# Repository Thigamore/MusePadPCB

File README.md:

# MusePadPCB  
  
  A small PCB which contains 4 keys so that I can try and make it irl and play muse dash, a rythm game with it.  
  Used to learn more about the basics of Electrical Engineering and the cool computer parts.

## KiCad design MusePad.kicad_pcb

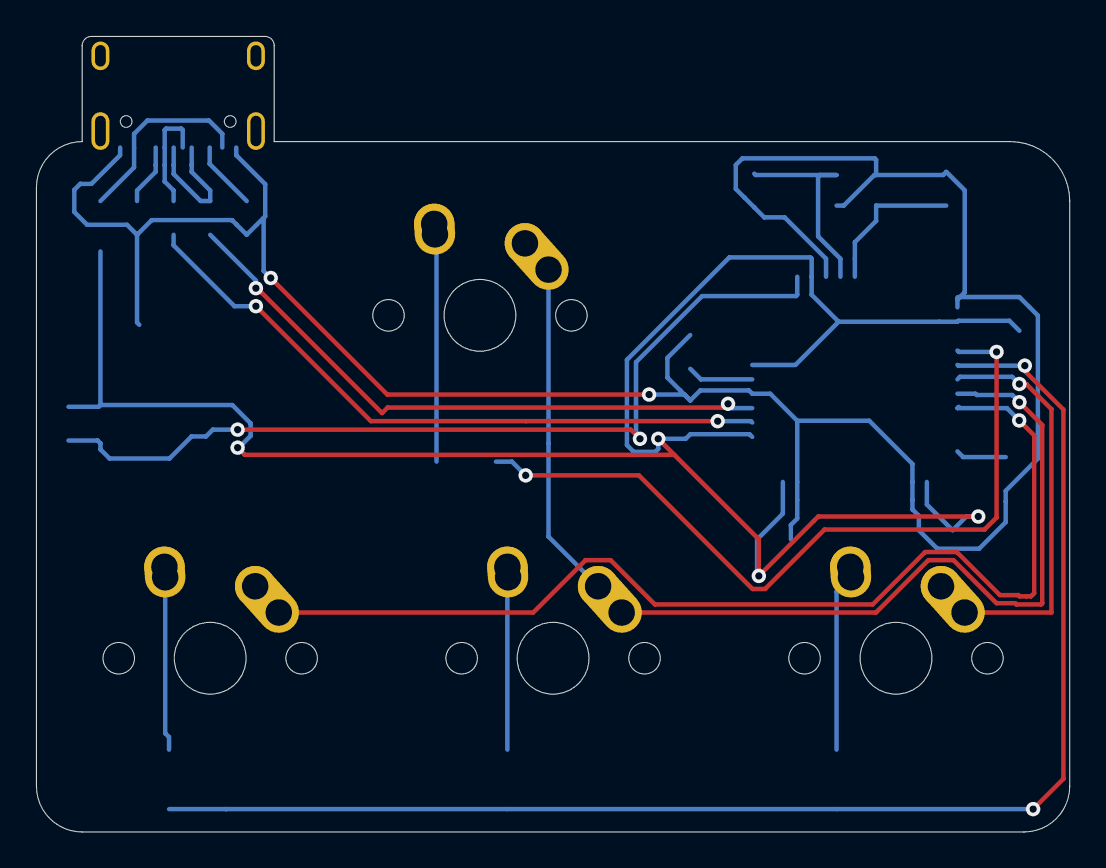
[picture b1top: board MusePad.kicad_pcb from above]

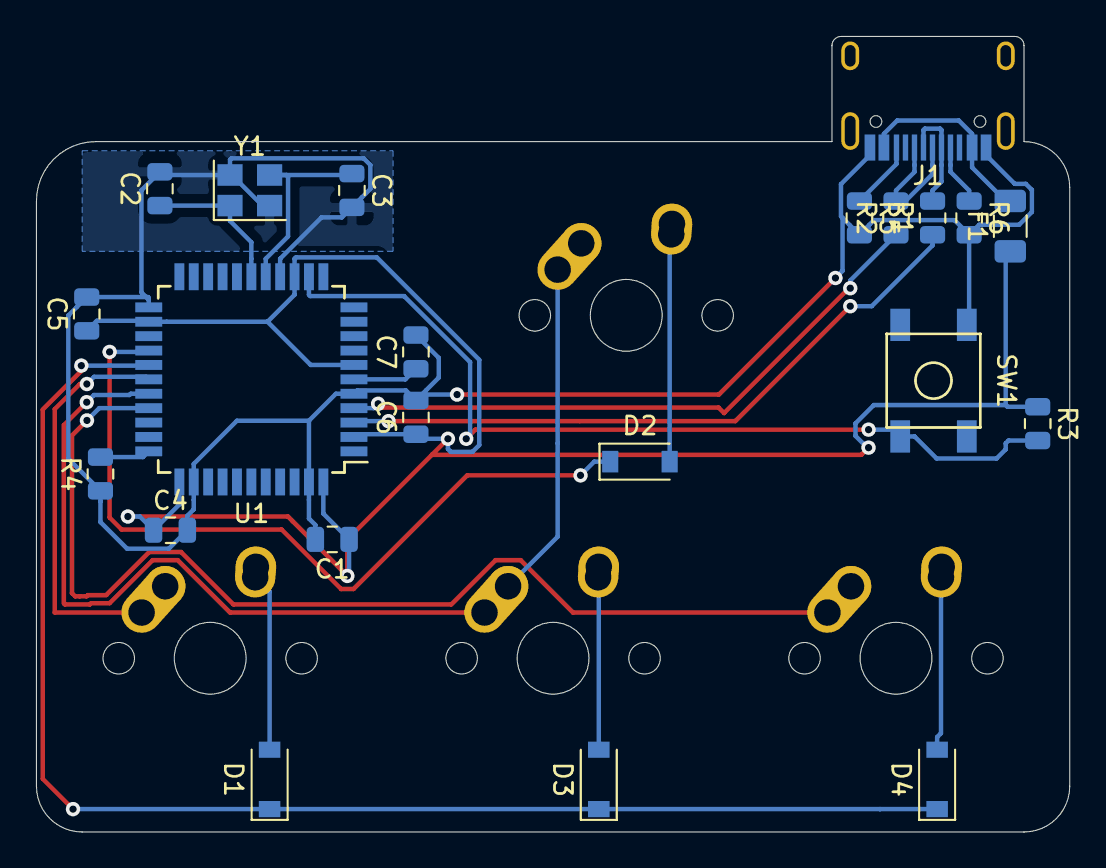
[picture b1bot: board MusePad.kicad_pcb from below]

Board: 2 copper layers, 57.4 x 44.2 mm, 26 parts (26 on the bottom side), 23 nets.

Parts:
C1, C4, C5: 0.1uF; C_0805_2012Metric
C2, C3: 22pF; C_0805_2012Metric
C6: 10uF; C_0805_2012Metric
C7: 1uF; C_0805_2012Metric
D1, D2, D3, D4: D_Small; D_SOD-123
F1: 500mA; Fuse_1206_3216Metric
J1: USB_C_Receptacle_USB2.0; HRO-TYPE-C-31-M-12
MX1, MX2, MX3, MX4: MX-NoLED; MX-1U-NoLED
R1, R2: 22; R_0805_2012Metric
R3: 10K; R_0805_2012Metric
R4: 10k; R_0805_2012Metric
R5, R6: 5k1; R_0805_2012Metric
SW1: SW_Push; SKQG-1155865
U1: ATmega32U4-AU; TQFP-44_10x10mm_P0.8mm
Y1: Crystal_GND24_Small; Crystal_SMD_3225-4Pin_3.2x2.5mm

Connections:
+5V: C1.1, C4.1, C5.1, C6.1, F1.1, R3.1, U1.2, U1.7, U1.14, U1.24, U1.34, U1.44
/COL0: MX1.1, U1.28
/COL1: MX2.1, MX3.1, U1.29
/COL2: MX4.1, U1.30
/D+: J1.A6, J1.B6, R2.2
/D-: J1.A7, J1.B7, R1.2
/ROW0: D2.1, U1.26
/ROW1: D1.1, D3.1, D4.1, U1.27
GND: C1.2, C2.2, C3.2, C4.2, C5.2, C6.2, C7.2, J1.A1, J1.A12, R4.1, R5.2, R6.2, SW1.1, U1.5, U1.15, U1.23, U1.35, U1.43, Y1.2, Y1.4
unnamed: C2.1, U1.17, Y1.1
unnamed: C3.1, U1.16, Y1.3
unnamed: C7.1, U1.6
unnamed: D1.2, MX1.2
unnamed: D2.2, MX2.2
unnamed: D3.2, MX3.2
unnamed: D4.2, MX4.2
unnamed: J1.A5, R6.1
unnamed: J1.B5, R5.1
unnamed: R1.1, U1.3
unnamed: R2.1, U1.4
unnamed: R3.2, SW1.2, U1.13
unnamed: R4.2, U1.33
VCC: F1.2, J1.A4, J1.A9

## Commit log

2022-10-20 Init
2022-10-20 gerber
